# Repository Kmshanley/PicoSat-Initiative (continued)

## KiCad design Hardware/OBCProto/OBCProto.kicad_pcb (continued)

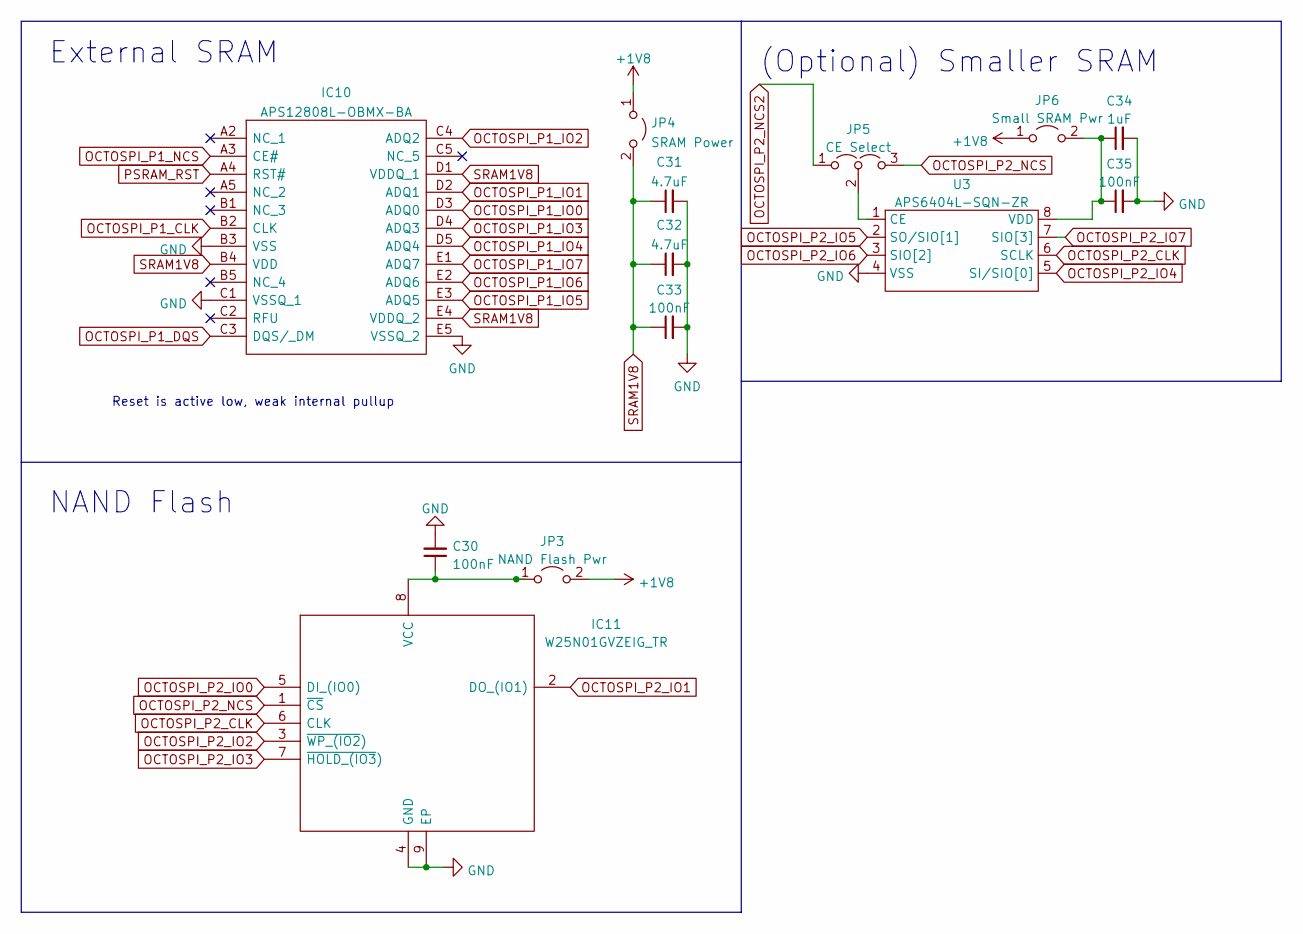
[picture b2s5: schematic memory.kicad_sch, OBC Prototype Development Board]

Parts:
C30, C33, C35: 100nF; C_0402_1005Metric
C31, C32: 4.7uF; C_0402_1005Metric
C34: 1uF; C_0402_1005Metric
IC10: APS12808L-OBMX-BA; BGA24C100P5X5_600X800X120; Mouser Part Number 878-APS12808L-OBMXBA
IC11: W25N01GVZEIG_TR; SON127P800X600X80-9N-D; Mouser Part Number 454-W25N01GVZEIGTR
JP3: NAND Flash Pwr; PinHeader_1x02_P2.54mm_Vertical
JP4: SRAM Power; PinHeader_1x02_P2.54mm_Vertical
JP5: CE Select; PinHeader_1x03_P2.54mm_Vertical
JP6: Small SRAM Pwr; PinHeader_1x02_P2.54mm_Vertical
U3: APS6404L-SQN-ZR

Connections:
+1V8: JP3.2 (B), JP4.1 (A), JP6.1 (A); also elsewhere on the board
GND: C30.2, C31.2, C32.2, C33.2, C34.2, C35.2, IC10.B3 (VSS), IC10.C1 (VSSQ_1), IC10.E5 (VSSQ_2), IC11.4 (GND), IC11.9 (EP), U3.4 (VSS); also elsewhere on the board
unnamed: C30.1, IC11.8 (VCC), JP3.1 (A)
unnamed: C34.1, C35.1, JP6.2 (B), U3.8 (VDD)
unnamed: JP5.2 (C), U3.1 (CE)
OCTOSPI_P1_CLK: IC10.B2 (CLK); also elsewhere on the board
OCTOSPI_P1_DQS: IC10.C3 (DQS/_DM); also elsewhere on the board
OCTOSPI_P1_IO0: IC10.D3 (ADQ0); also elsewhere on the board
OCTOSPI_P1_IO1: IC10.D2 (ADQ1); also elsewhere on the board
OCTOSPI_P1_IO2: IC10.C4 (ADQ2); also elsewhere on the board
OCTOSPI_P1_IO3: IC10.D4 (ADQ3); also elsewhere on the board
OCTOSPI_P1_IO4: IC10.D5 (ADQ4); also elsewhere on the board
OCTOSPI_P1_IO5: IC10.E3 (ADQ5); also elsewhere on the board
OCTOSPI_P1_IO6: IC10.E2 (ADQ6); also elsewhere on the board
OCTOSPI_P1_IO7: IC10.E1 (ADQ7); also elsewhere on the board
OCTOSPI_P1_NCS: IC10.A3 (CE#); also elsewhere on the board
OCTOSPI_P2_CLK: IC11.6 (CLK), U3.6 (SCLK); also elsewhere on the board
OCTOSPI_P2_IO0: IC11.5 (DI_(IO0)); also elsewhere on the board
OCTOSPI_P2_IO1: IC11.2 (DO_(IO1)); also elsewhere on the board
OCTOSPI_P2_IO2: IC11.3 (~WP_(IO2)); also elsewhere on the board
OCTOSPI_P2_IO3: IC11.7 (~HOLD_(IO3)); also elsewhere on the board
OCTOSPI_P2_IO4: U3.5 (SI/SIO[0]); also elsewhere on the board
OCTOSPI_P2_IO5: U3.2 (SO/SIO[1]); also elsewhere on the board
OCTOSPI_P2_IO6: U3.3 (SIO[2]); also elsewhere on the board
OCTOSPI_P2_NCS: IC11.1 (~CS), JP5.3 (B); also elsewhere on the board
OCTOSPI_P2_NCS2: JP5.1 (A); also elsewhere on the board
PSRAM_RST: IC10.A4 (RST#); also elsewhere on the board
SRAM1V8: C31.1, C32.1, C33.1, IC10.B4 (VDD), IC10.D1 (VDDQ_1), IC10.E4 (VDDQ_2), JP4.2 (B)

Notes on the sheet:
External SRAM
Reset is active low, weak internal pullup
(Optional) Smaller SRAM
NAND Flash

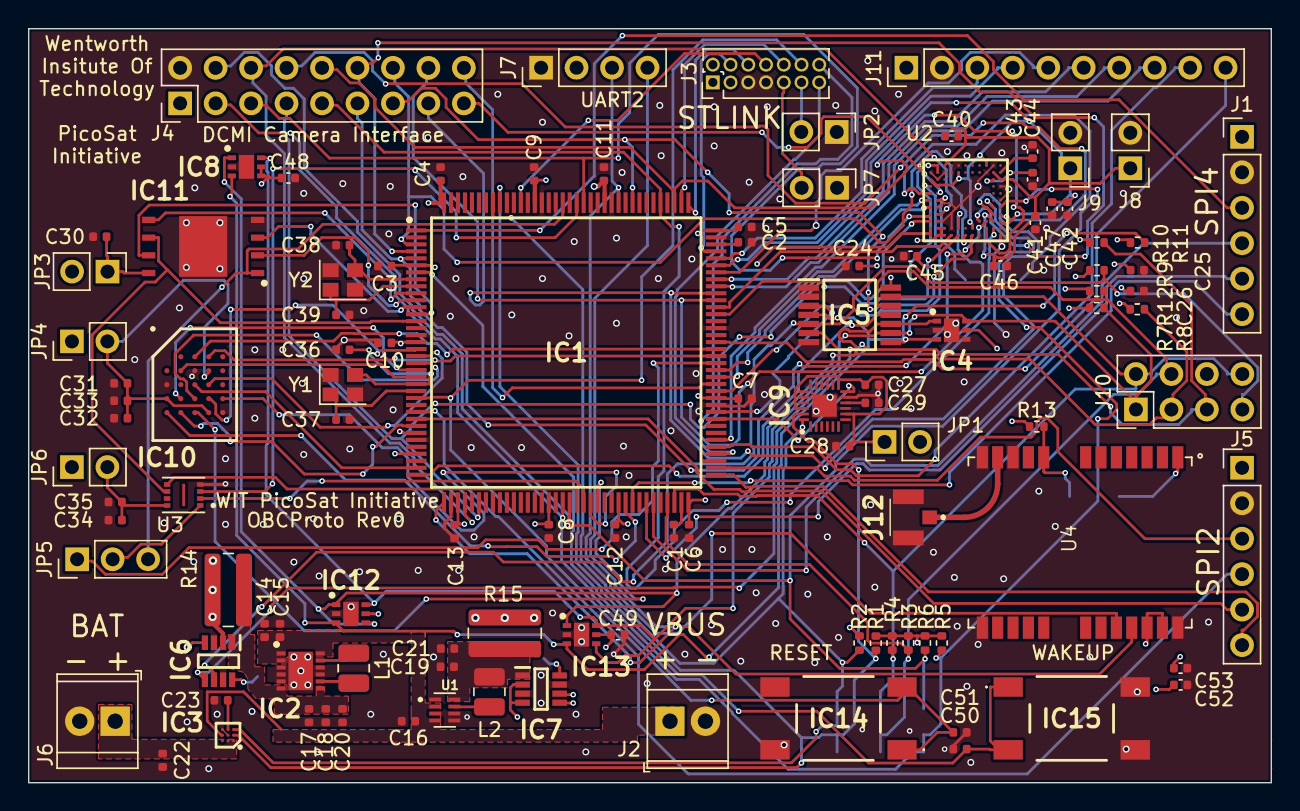
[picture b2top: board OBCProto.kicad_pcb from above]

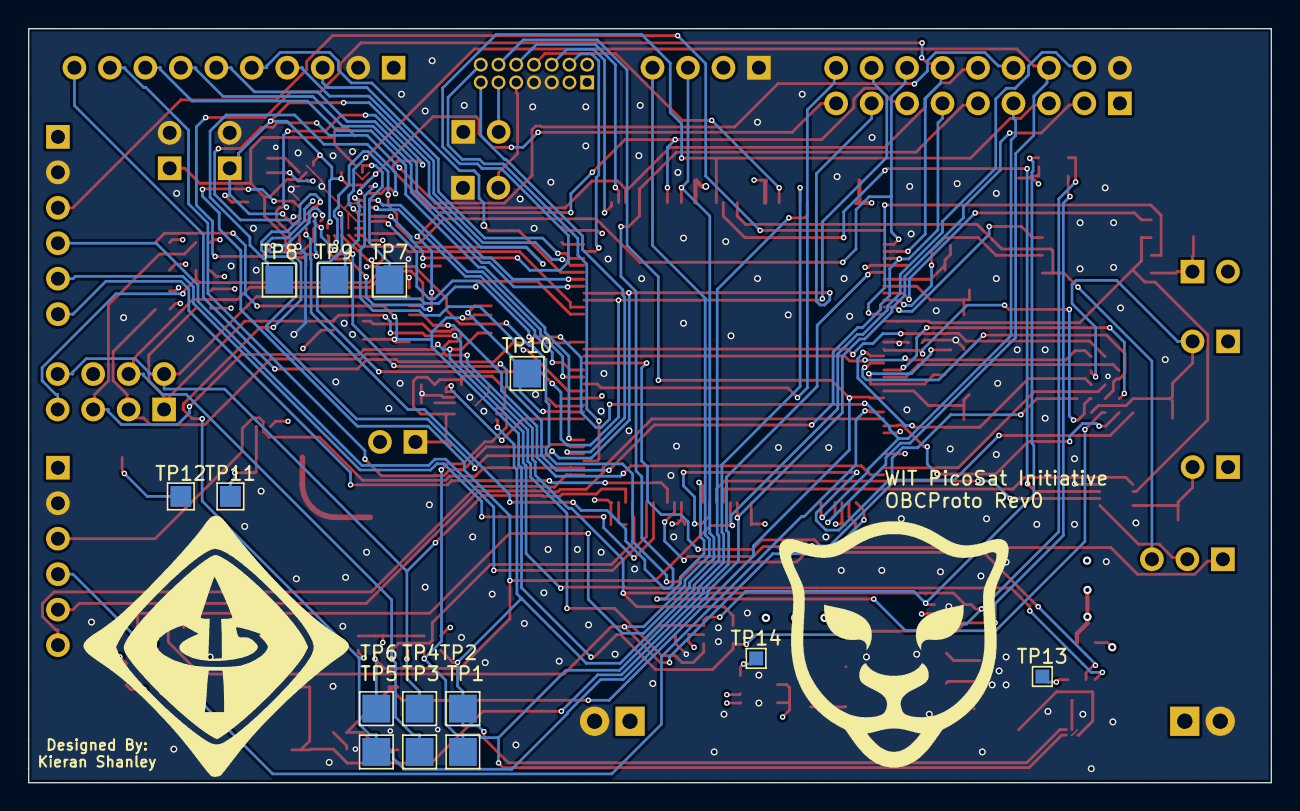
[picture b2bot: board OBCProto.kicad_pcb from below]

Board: 4 copper layers, 89.0 x 54.0 mm, 124 parts (14 on the bottom side), 118 nets.

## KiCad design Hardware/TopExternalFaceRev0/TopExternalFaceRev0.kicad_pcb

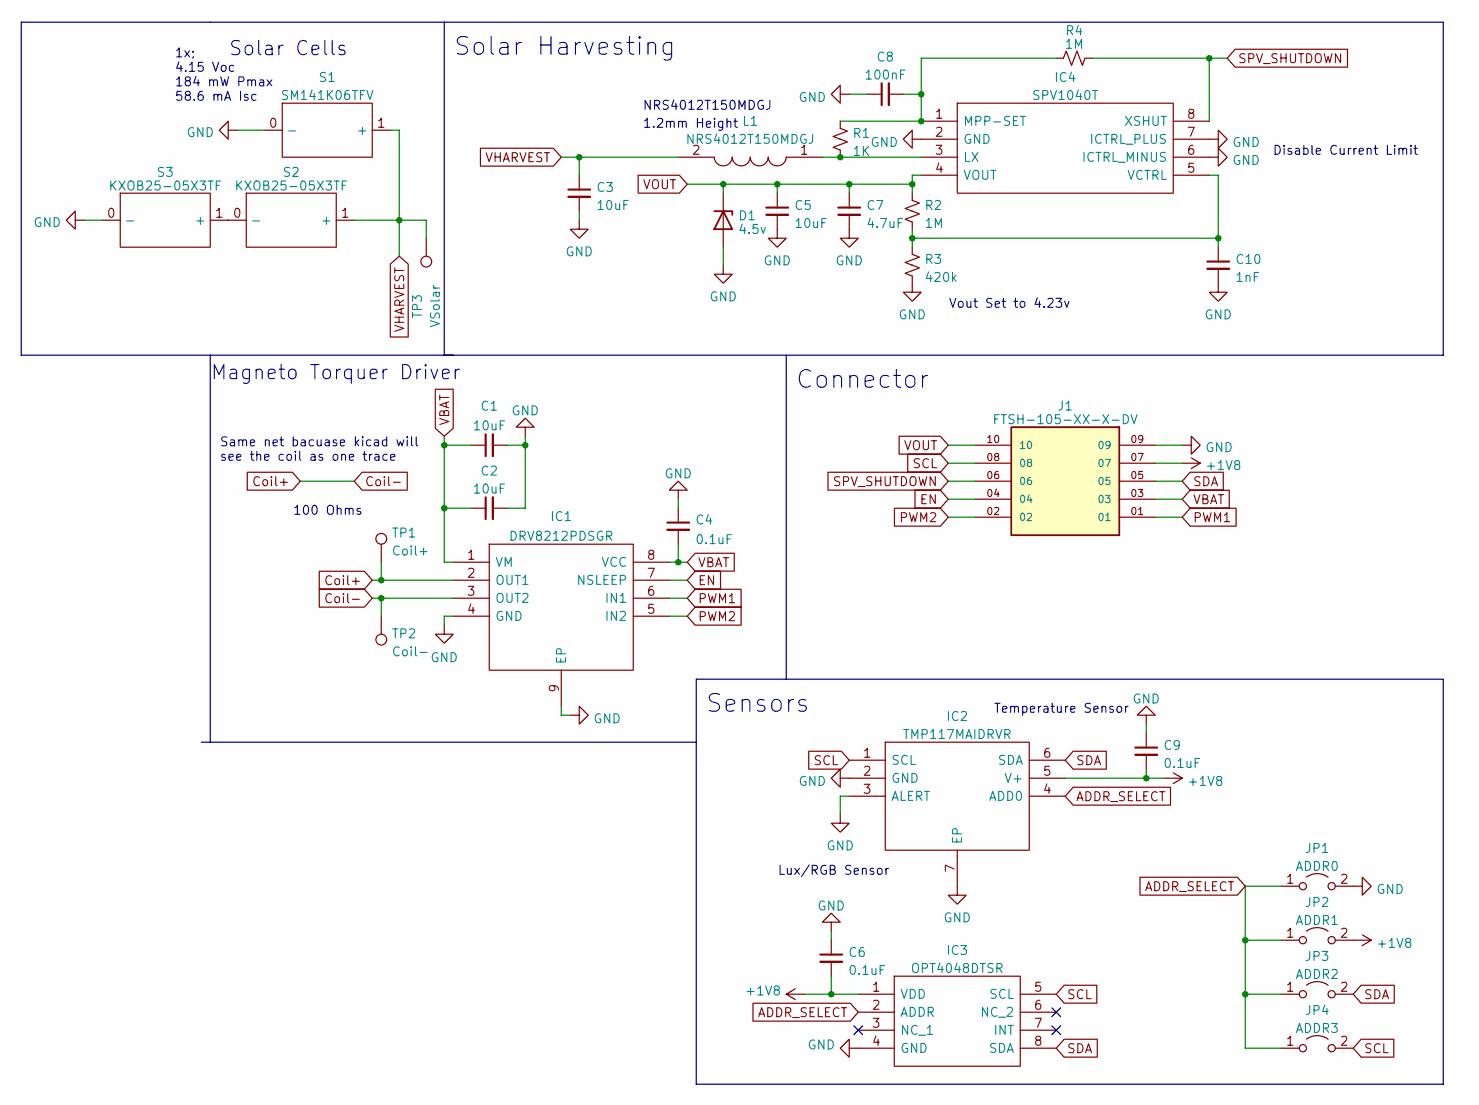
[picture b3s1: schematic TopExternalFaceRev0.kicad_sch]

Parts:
C1, C2, C3, C5: 10uF; C_0402_1005Metric
C4, C6, C9: 0.1uF; C_0402_1005Metric
C7: 4.7uF; C_0402_1005Metric
C8: 100nF; C_0402_1005Metric
C10: 1nF; C_0402_1005Metric
D1: 4.5v; D_SOD-123
IC1: DRV8212PDSGR; SON50P200X200X80-9N; Mouser Part Number 595-DRV8212PDSGR
IC2: TMP117MAIDRVR; SON65P200X200X80-7N; Mouser Part Number 595-TMP117MAIDRVR
IC3: OPT4048DTSR; SOTFL50P190X60-8N; Mouser Part Number 595-OPT4048DTSR
IC4: SPV1040T; SOP65P640X120-8N; Mouser Part Number 511-SPV1040T
J1: FTSH-105-XX-X-DV; SAMTEC_FTSH-105-XX-X-DV; PARTREV H
JP1: ADDR0; SolderJumper-2_P1.3mm_Open_Pad1.0x1.5mm
JP2: ADDR1; SolderJumper-2_P1.3mm_Open_Pad1.0x1.5mm
JP3: ADDR2; SolderJumper-2_P1.3mm_Open_Pad1.0x1.5mm
JP4: ADDR3; SolderJumper-2_P1.3mm_Open_Pad1.0x1.5mm
L1: NRS4012T150MDGJ; Mouser Part Number 963-NRS4012T150MDGJ
R1: 1K; R_0402_1005Metric
R2, R4: 1M; R_0402_1005Metric
R3: 420k; R_0402_1005Metric
S1: SM141K06TFV
S2, S3: KXOB25-05X3TF
TP1: Coil+; TestPoint_Pad_D2.0mm
TP2: Coil-; TestPoint_Pad_D2.0mm
TP3: VSolar; TestPoint_Pad_1.0x1.0mm

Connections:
+1V8: C6.2, C9.2, IC2.5 (V+), IC3.1 (VDD), J1.07, JP2.2 (B)
ADDR_SELECT: IC2.4 (ADD0), IC3.2 (ADDR), JP1.1 (A), JP2.1 (A), JP3.1 (A), JP4.1 (A)
Coil+: IC1.2 (OUT1), IC1.3 (OUT2), TP1.1, TP2.1
EN: IC1.7 (NSLEEP), J1.04
GND: C1.2, C2.2, C3.2, C4.1, C5.2, C6.1, C7.2, C8.1, C9.1, C10.2, D1.2 (A), IC1.4 (GND), IC1.9 (EP), IC2.2 (GND), IC2.3 (ALERT), IC2.7 (EP), IC3.4 (GND), IC4.2 (GND), IC4.6 (ICTRL_MINUS), IC4.7 (ICTRL_PLUS), J1.09, JP1.2 (B), R3.2, S1.0 (-), S3.0 (-)
unnamed: IC4.3 (LX), L1.1, R1.2
unnamed: C8.2, IC4.1 (MPP-SET), R1.1, R4.1
unnamed: C10.1, IC4.5 (VCTRL), R2.2, R3.1
unnamed: S2.0 (-), S3.1 (+)
PWM1: IC1.6 (IN1), J1.01
PWM2: IC1.5 (IN2), J1.02
SCL: IC2.1 (SCL), IC3.5 (SCL), J1.08, JP4.2 (B)
SDA: IC2.6 (SDA), IC3.8 (SDA), J1.05, JP3.2 (B)
SPV_SHUTDOWN: IC4.8 (XSHUT), J1.06, R4.2
VBAT: C1.1, C2.1, C4.2, IC1.1 (VM), IC1.8 (VCC), J1.03
VHARVEST: C3.1, L1.2, S1.1 (+), S2.1 (+), TP3.1
VOUT: C5.1, C7.1, D1.1 (K), IC4.4 (VOUT), J1.10, R2.1

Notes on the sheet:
Lux/RGB Sensor
Sensors
100 Ohms
Vout Set to 4.23v
Solar Cells
Disable Current Limit
1.2mm Height
Solar Harvesting
NRS4012T150MDGJ
Same net bacuase kicad will see the coil as one trace
Magneto Torquer Driver
Connector
1x; 4.15 Voc 184 mW Pmax 58.6 mA Isc
Temperature Sensor

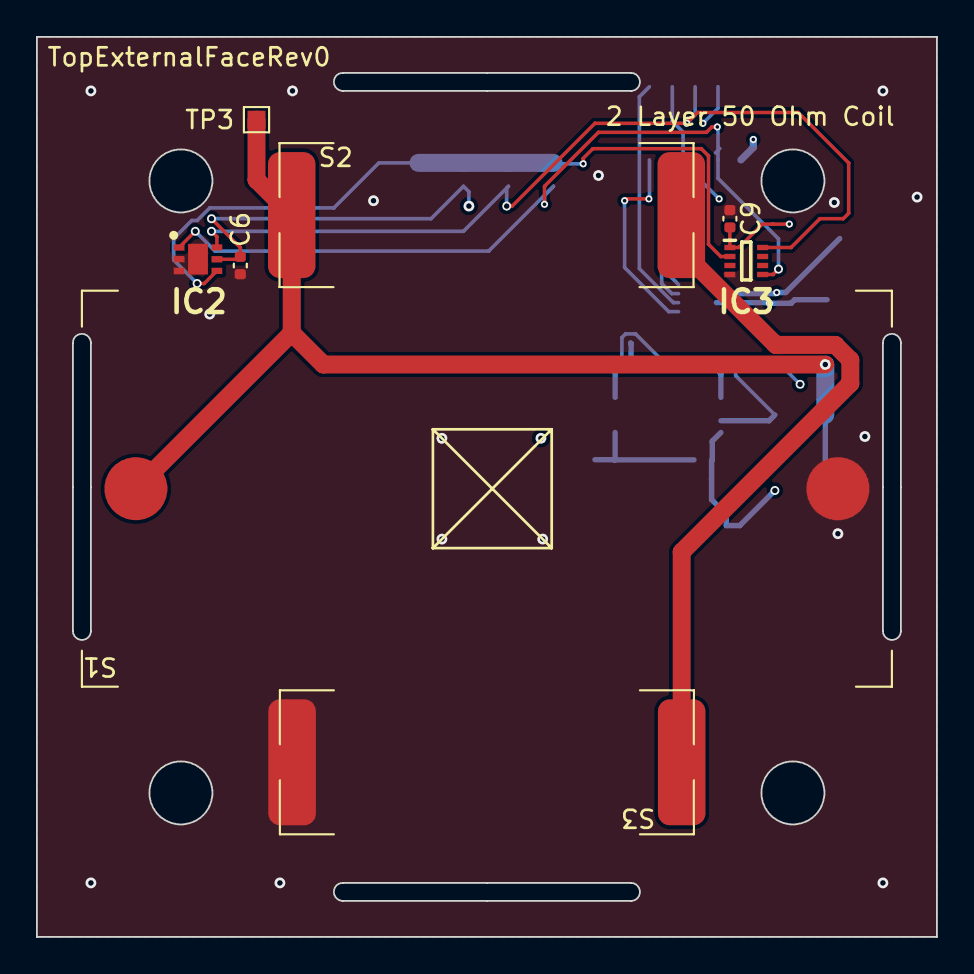
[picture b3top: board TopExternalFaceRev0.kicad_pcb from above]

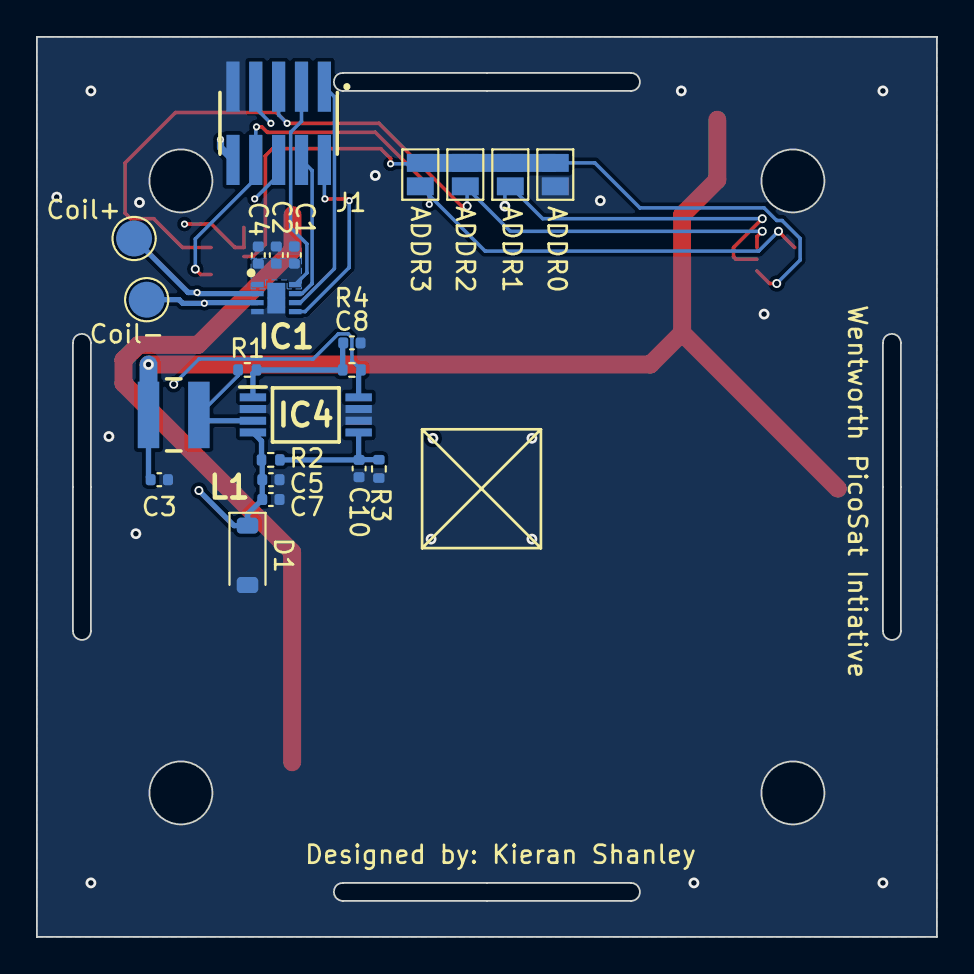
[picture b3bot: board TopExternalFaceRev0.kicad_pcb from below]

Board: 4 copper layers, 50.0 x 50.0 mm, 31 parts (23 on the bottom side), 17 nets.

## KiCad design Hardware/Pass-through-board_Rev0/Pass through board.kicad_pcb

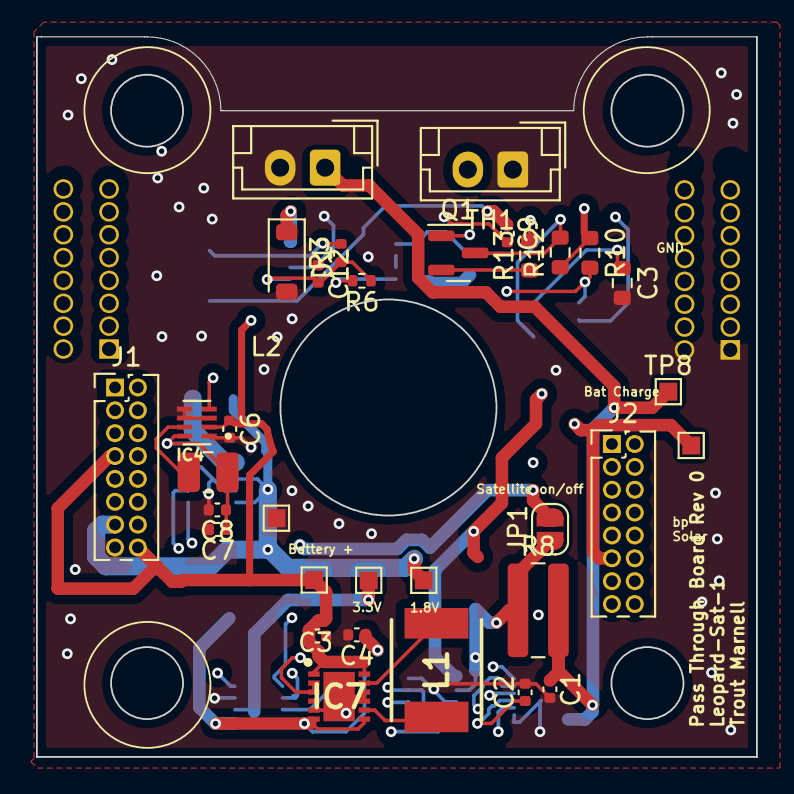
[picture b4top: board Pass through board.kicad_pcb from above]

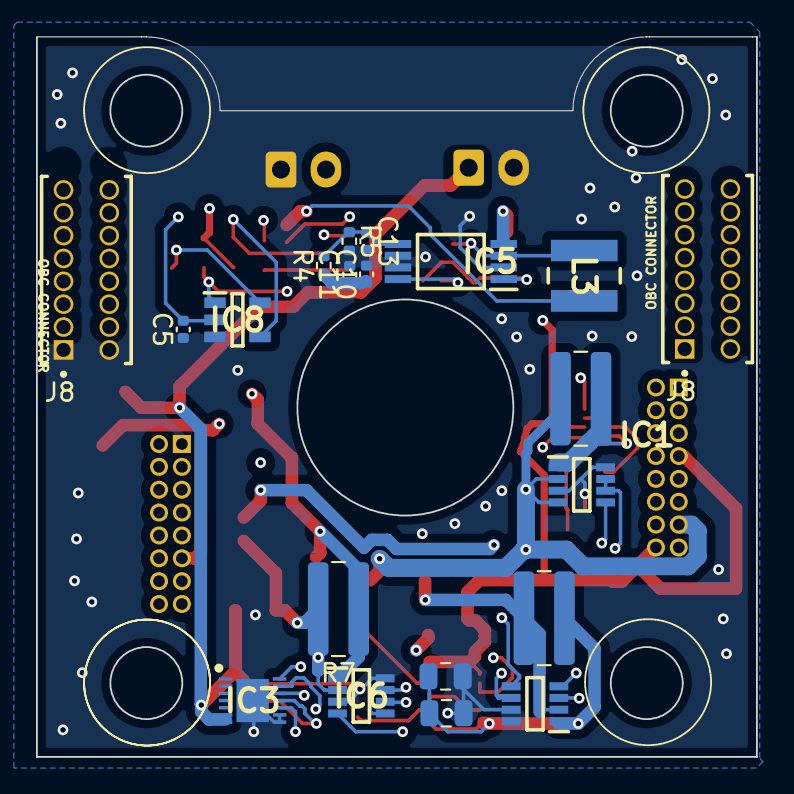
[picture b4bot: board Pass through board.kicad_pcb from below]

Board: 4 copper layers, 40.0 x 40.0 mm, 53 parts (20 on the bottom side), 26 nets.

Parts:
C1: .1uF; C_0402_1005Metric
C2: .47uF; C_0402_1005Metric
C3: 10uF; R_0603_1608Metric
C3#2, C7, C9, C10: 10uF; C_0402_1005Metric
C4: 22uF; C_0402_1005Metric
C5, C8: 1uF; C_0402_1005Metric
C6, C11: 4.7uF; C_0402_1005Metric
C12: 100nF; C_0402_1005Metric
C13: 1nF; C_0402_1005Metric
D1: 4.5v; D_SOD-123
IC1, IC2, IC6: INA236AIDDFR; SOP65P280X110-8N
IC3: MAX17260SETD+T; SON40P300X300X80-15N
IC4: TPS62840DLCR; SON50P200X150X100-8N
IC5: SPV1040T; SOP65P640X120-8N
IC7: RP602K330G-TR; SON50P270X300X60-13N
IC8: TLV840MADL30DBVRQ1; SOT95P280X145-5N
J1, J2: FLE-108-01-XX-DV; PinHeader_2x08_P1.27mm_Vertical
J3: Conn_01x02_Socket; JST_EH_B2B-EH-A_1x02_P2.50mm_Vertical
J8, J8#2: SLM-108-01-L-D; SAMTEC_SLM-108-01-L-D
JP1: SolderJumper_2_Open; SolderJumper-2_P1.3mm_Open_RoundedPad1.0x1.5mm
L1: 1.0uH; INDPM5650X530N
L2: 2.2uH; L_1008_2520Metric
L3: NRS4012T150MDGJ
Q1: 2N7002; SOT-23
R1, R2, R7: 20m; R_1020_2550Metric
R3: 1K; R_0402_1005Metric
R4, R6: 1M; R_0402_1005Metric
R5: 420k; R_0402_1005Metric
R8: 10m; R_1020_2550Metric
R10, R12: 1M; R_0603_1608Metric
R13: 5k; R_0603_1608Metric
TH1: Thermistor_NTC 10k; JST_EH_B2B-EH-A_1x02_P2.50mm_Vertical
TP1, TP2, TP3, TP4, TP6, TP8: TestPoint_Alt; TestPoint_Pad_1.0x1.0mm
ff: C_0805_2012Metric
gg: C_0805_2012Metric

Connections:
1.8V: IC1.4 (VS), IC2.2 (IN-), IC2.4 (VS), IC6.4 (VS), J1.13, J2.5, Q1.1 (G), R2.2, R13.2, TP3.1
1V8 MEASURE: C7.1, C8.1, IC2.1 (IN+), IC4.8 (VOS), L2.2, R2.1
3.3V: C5.2, IC1.2 (IN-), IC8.2 (VDD), R1.2, TP2.1
3V3 MEASURE: C4.1, IC1.1 (IN+), IC7.6 (VFB), IC7.7 (VOUT), R1.1, ff.1, gg.1
Battery +: C3#2.2, C6.1, IC4.2 (VIN), IC7.1 (AVIN), IC7.12 (PVIN), J1.7, J1.16, R10.1, R12.1, TP1.1
Battery Charge: C1.1, IC3.6 (BATT), IC3.7 (CSN), J3.1, R8.2, TP8.1
CONV_SHUTDOWN: IC4.4 (EN), IC7.2 (CE), IC7.3 (MODE), IC8.1 (~RESET_/_RESET), R10.2
CT: C3.1, IC8.5 (CT)
GND: C1.2, C2.2, C3.2, C3#2.1, C4.2, C5.1, C6.2, C7.2, C8.2, C9.2, C10.2, C11.2, C12.1, C13.2, D1.2 (A), IC1.3 (GND), IC1.7 (A0), IC1.8 (ALERT), IC2.3 (GND), IC2.8 (ALERT), IC3.8 (GND), IC3.9 (CSPL), IC3.15 (EP), IC4.1 (GND), IC4.3 (MODE), IC4.5 (VSET), IC4.6 (STOP), IC5.2 (GND), IC5.6 (ICTRL_MINUS), IC5.7 (ICTRL_PLUS), IC6.3 (GND), IC6.8 (ALERT), IC7.5 (AGND), IC7.9 (PGND_1), IC7.10 (PGND_2), IC7.13 (GROUND), IC8.3 (GND), J1.15, J2.1, J3.2, R5.2, TH1.1, TP4.1, ff.2, gg.2
MPPT ENABLE: IC5.8 (XSHUT), R6.2
unnamed: C2.1, IC3.11 (REG)
unnamed: IC3.1 (TH), TH1.2
unnamed: IC4.7 (SW), L2.1
unnamed: IC5.3 (LX), L3.1, R3.2
unnamed: C12.2, IC5.1 (MPP-SET), R3.1, R6.1
unnamed: C13.1, IC5.5 (VCTRL), R4.2, R5.1
unnamed: IC7.8 (BOLX), L1.2
unnamed: IC7.11 (BULX), L1.1
unnamed: IC8.4 (~MR), Q1.3 (D), R12.2
SAT_REST: Q1.2 (S), R13.1
SCL(1): IC1.5 (SCL), IC2.5 (SCL), IC3.14 (SCL), IC6.5 (SCL), IC6.7 (A0), J1.1
SDA(1): IC1.6 (SDA), IC2.6 (SDA), IC2.7 (A0), IC3.13 (SDA), IC6.6 (SDA), J1.3
VBAT+: J1.14, J2.3, JP1.2 (B)
VMPPT: C10.1, C11.1, D1.1 (K), IC5.4 (VOUT), IC6.1 (IN+), J2.9, R4.1, R7.1
VMPPTCHARGE: IC3.10 (CSPH), IC6.2 (IN-), JP1.1 (A), R7.2, R8.1
Vsolar: C9.1, J2.11, L3.2, TP6.1

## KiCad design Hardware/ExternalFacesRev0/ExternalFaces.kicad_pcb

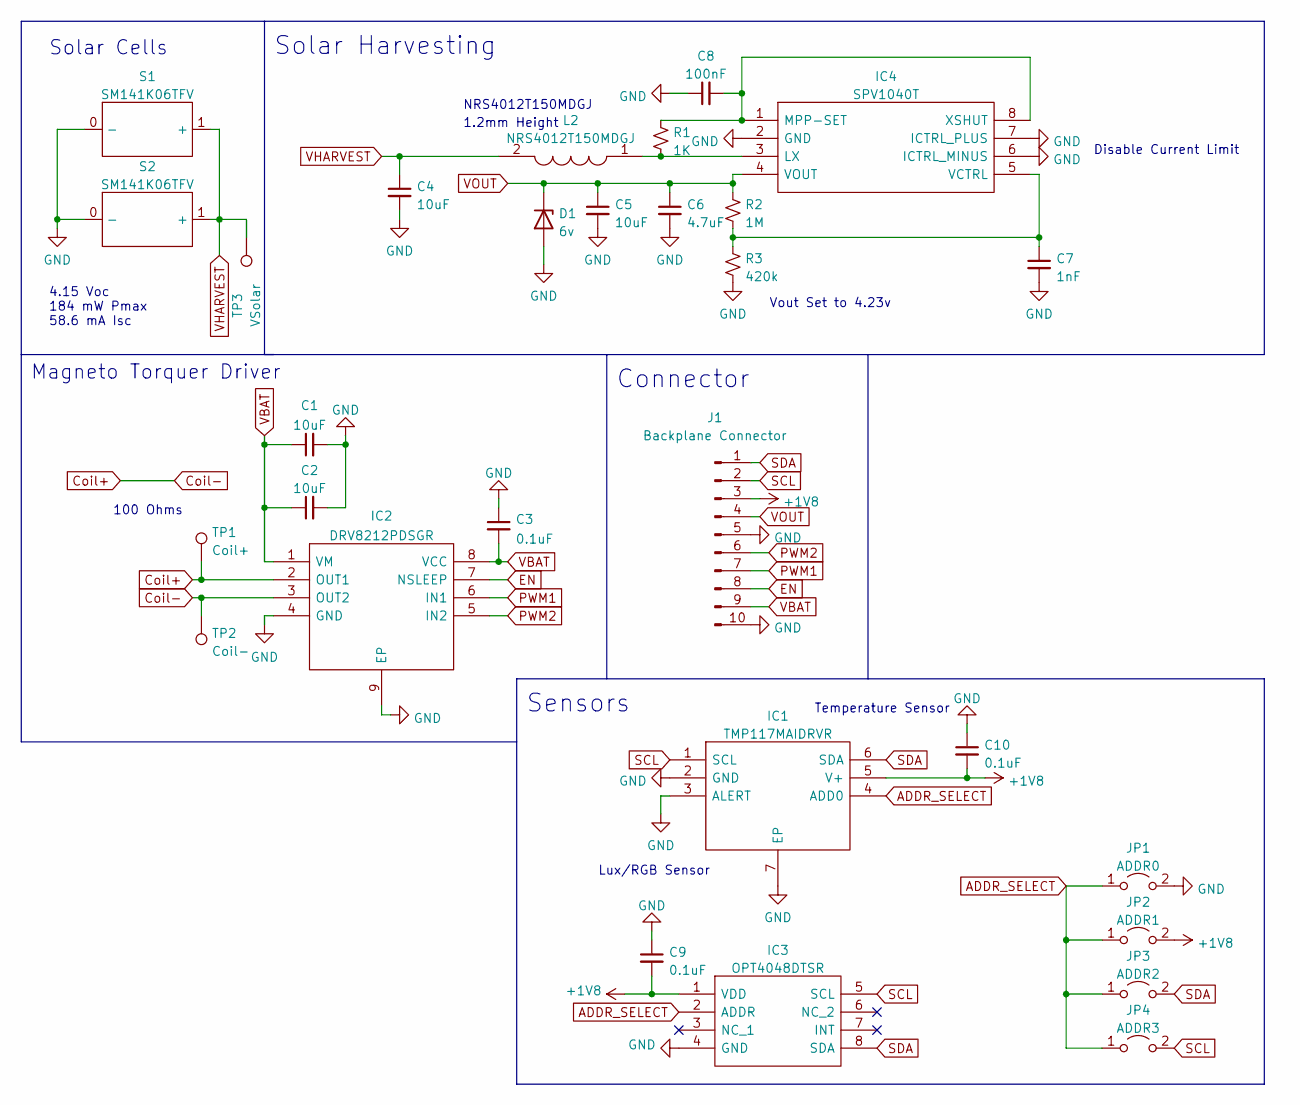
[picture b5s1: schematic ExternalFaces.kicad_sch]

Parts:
C1, C2, C4, C5: 10uF; C_0402_1005Metric
C3, C9, C10: 0.1uF; C_0402_1005Metric
C6: 4.7uF; C_0402_1005Metric
C7: 1nF; C_0402_1005Metric
C8: 100nF; C_0402_1005Metric
D1: 6v; D_SOD-123
IC1: TMP117MAIDRVR; SON65P200X200X80-7N; Mouser Part Number 595-TMP117MAIDRVR
IC2: DRV8212PDSGR; SON50P200X200X80-9N; Mouser Part Number 595-DRV8212PDSGR
IC3: OPT4048DTSR; SOTFL50P190X60-8N; Mouser Part Number 595-OPT4048DTSR
IC4: SPV1040T; SOP65P640X120-8N; Mouser Part Number 511-SPV1040T
J1: Backplane Connector; PinHeader_1x10_P1.00mm_Vertical
JP1: ADDR0; SolderJumper-2_P1.3mm_Open_Pad1.0x1.5mm
JP2: ADDR1; SolderJumper-2_P1.3mm_Open_Pad1.0x1.5mm
JP3: ADDR2; SolderJumper-2_P1.3mm_Open_Pad1.0x1.5mm
JP4: ADDR3; SolderJumper-2_P1.3mm_Open_Pad1.0x1.5mm
L2: NRS4012T150MDGJ; Mouser Part Number 963-NRS4012T150MDGJ
R1: 1K; R_0402_1005Metric
R2: 1M; R_0402_1005Metric
R3: 420k; R_0402_1005Metric
S1, S2: SM141K06TFV
TP1: Coil+; TestPoint_Pad_D2.0mm
TP2: Coil-; TestPoint_Pad_D2.0mm
TP3: VSolar; TestPoint_Pad_1.0x1.0mm

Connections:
+1V8: C9.2, C10.2, IC1.5 (V+), IC3.1 (VDD), J1.3, JP2.2 (B)
ADDR_SELECT: IC1.4 (ADD0), IC3.2 (ADDR), JP1.1 (A), JP2.1 (A), JP3.1 (A), JP4.1 (A)
Coil+: IC2.2 (OUT1), IC2.3 (OUT2), TP1.1, TP2.1
EN: IC2.7 (NSLEEP), J1.8
GND: C1.2, C2.2, C3.1, C4.2, C5.2, C6.2, C7.2, C8.1, C9.1, C10.1, D1.2 (A), IC1.2 (GND), IC1.3 (ALERT), IC1.7 (EP), IC2.4 (GND), IC2.9 (EP), IC3.4 (GND), IC4.2 (GND), IC4.6 (ICTRL_MINUS), IC4.7 (ICTRL_PLUS), J1.5, J1.10, JP1.2 (B), R3.2, S1.0 (-), S2.0 (-)
unnamed: C7.1, IC4.5 (VCTRL), R2.2, R3.1
unnamed: C8.2, IC4.1 (MPP-SET), IC4.8 (XSHUT), R1.1
unnamed: IC4.3 (LX), L2.1, R1.2
PWM1: IC2.6 (IN1), J1.7
PWM2: IC2.5 (IN2), J1.6
SCL: IC1.1 (SCL), IC3.5 (SCL), J1.2, JP4.2 (B)
SDA: IC1.6 (SDA), IC3.8 (SDA), J1.1, JP3.2 (B)
VBAT: C1.1, C2.1, C3.2, IC2.1 (VM), IC2.8 (VCC), J1.9
VHARVEST: C4.1, L2.2, S1.1 (+), S2.1 (+), TP3.1
VOUT: C5.1, C6.1, D1.1 (K), IC4.4 (VOUT), J1.4, R2.1

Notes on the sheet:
Lux/RGB Sensor
4.15 Voc 184 mW Pmax 58.6 mA Isc
1.2mm Height
Solar Harvesting
Magneto Torquer Driver
Vout Set to 4.23v
Solar Cells
Sensors
Temperature Sensor
Disable Current Limit
Connector
100 Ohms
NRS4012T150MDGJ

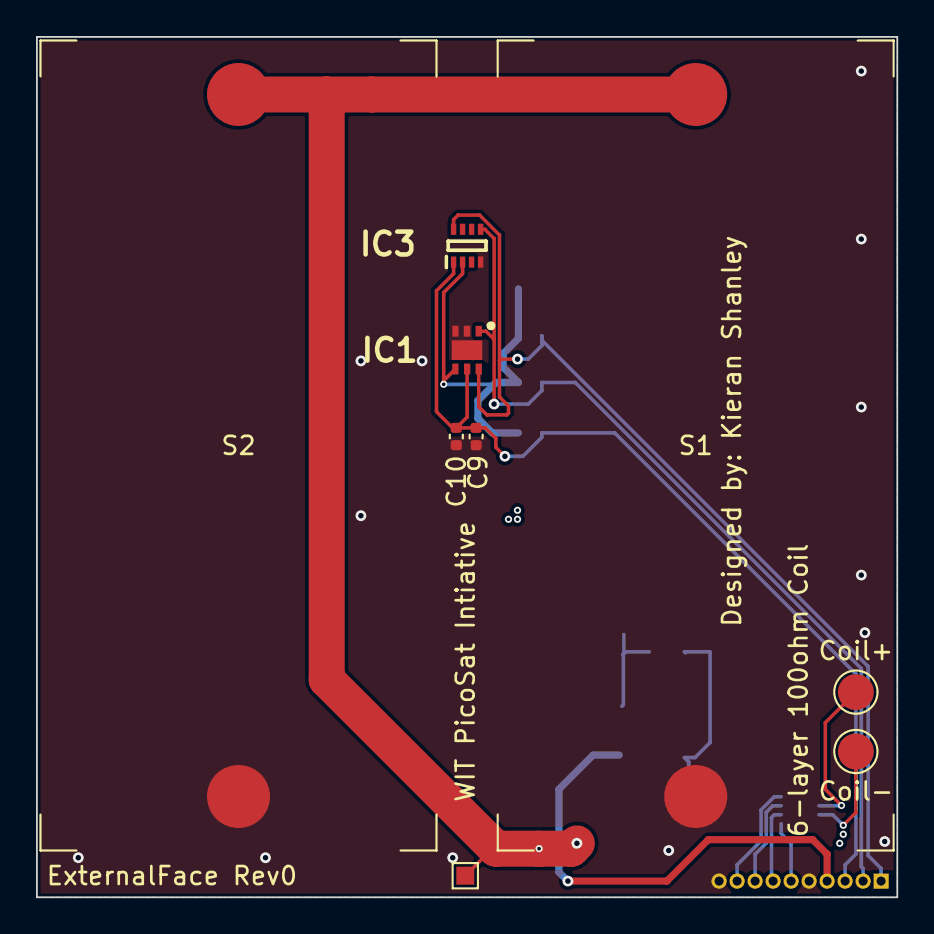
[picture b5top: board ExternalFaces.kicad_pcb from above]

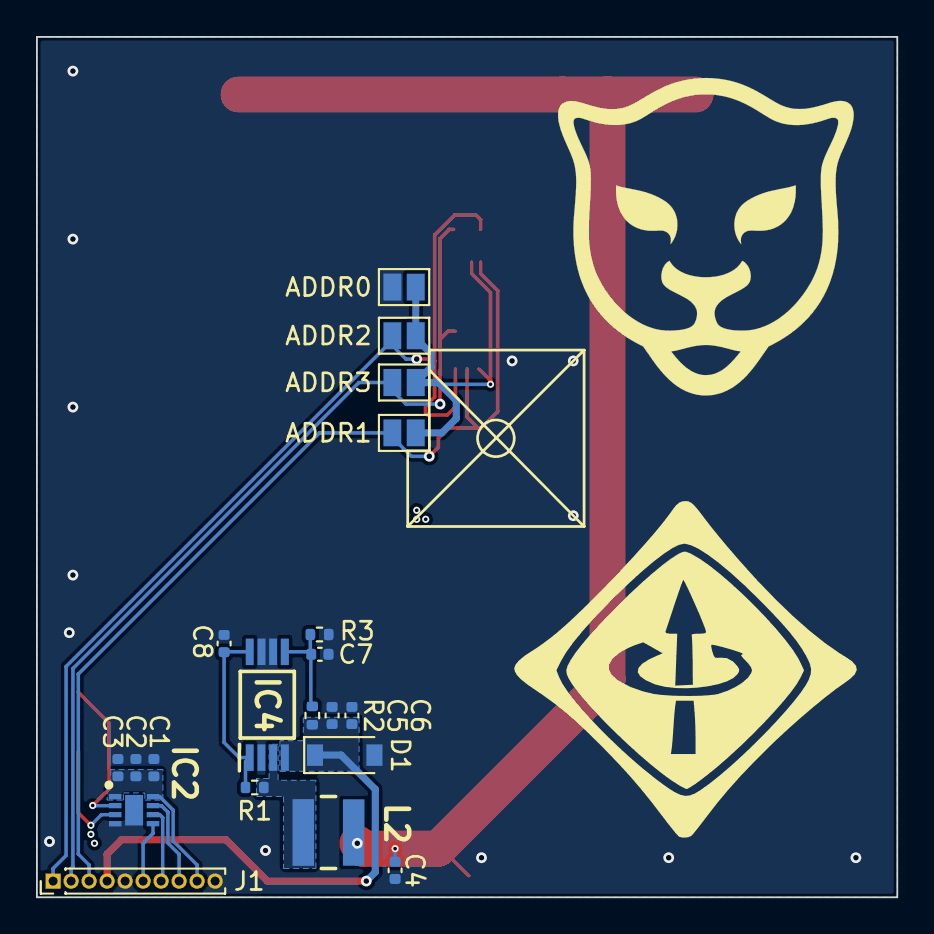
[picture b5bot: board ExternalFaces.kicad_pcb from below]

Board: 8 copper layers, 47.8 x 47.8 mm, 29 parts (20 on the bottom side), 15 nets.

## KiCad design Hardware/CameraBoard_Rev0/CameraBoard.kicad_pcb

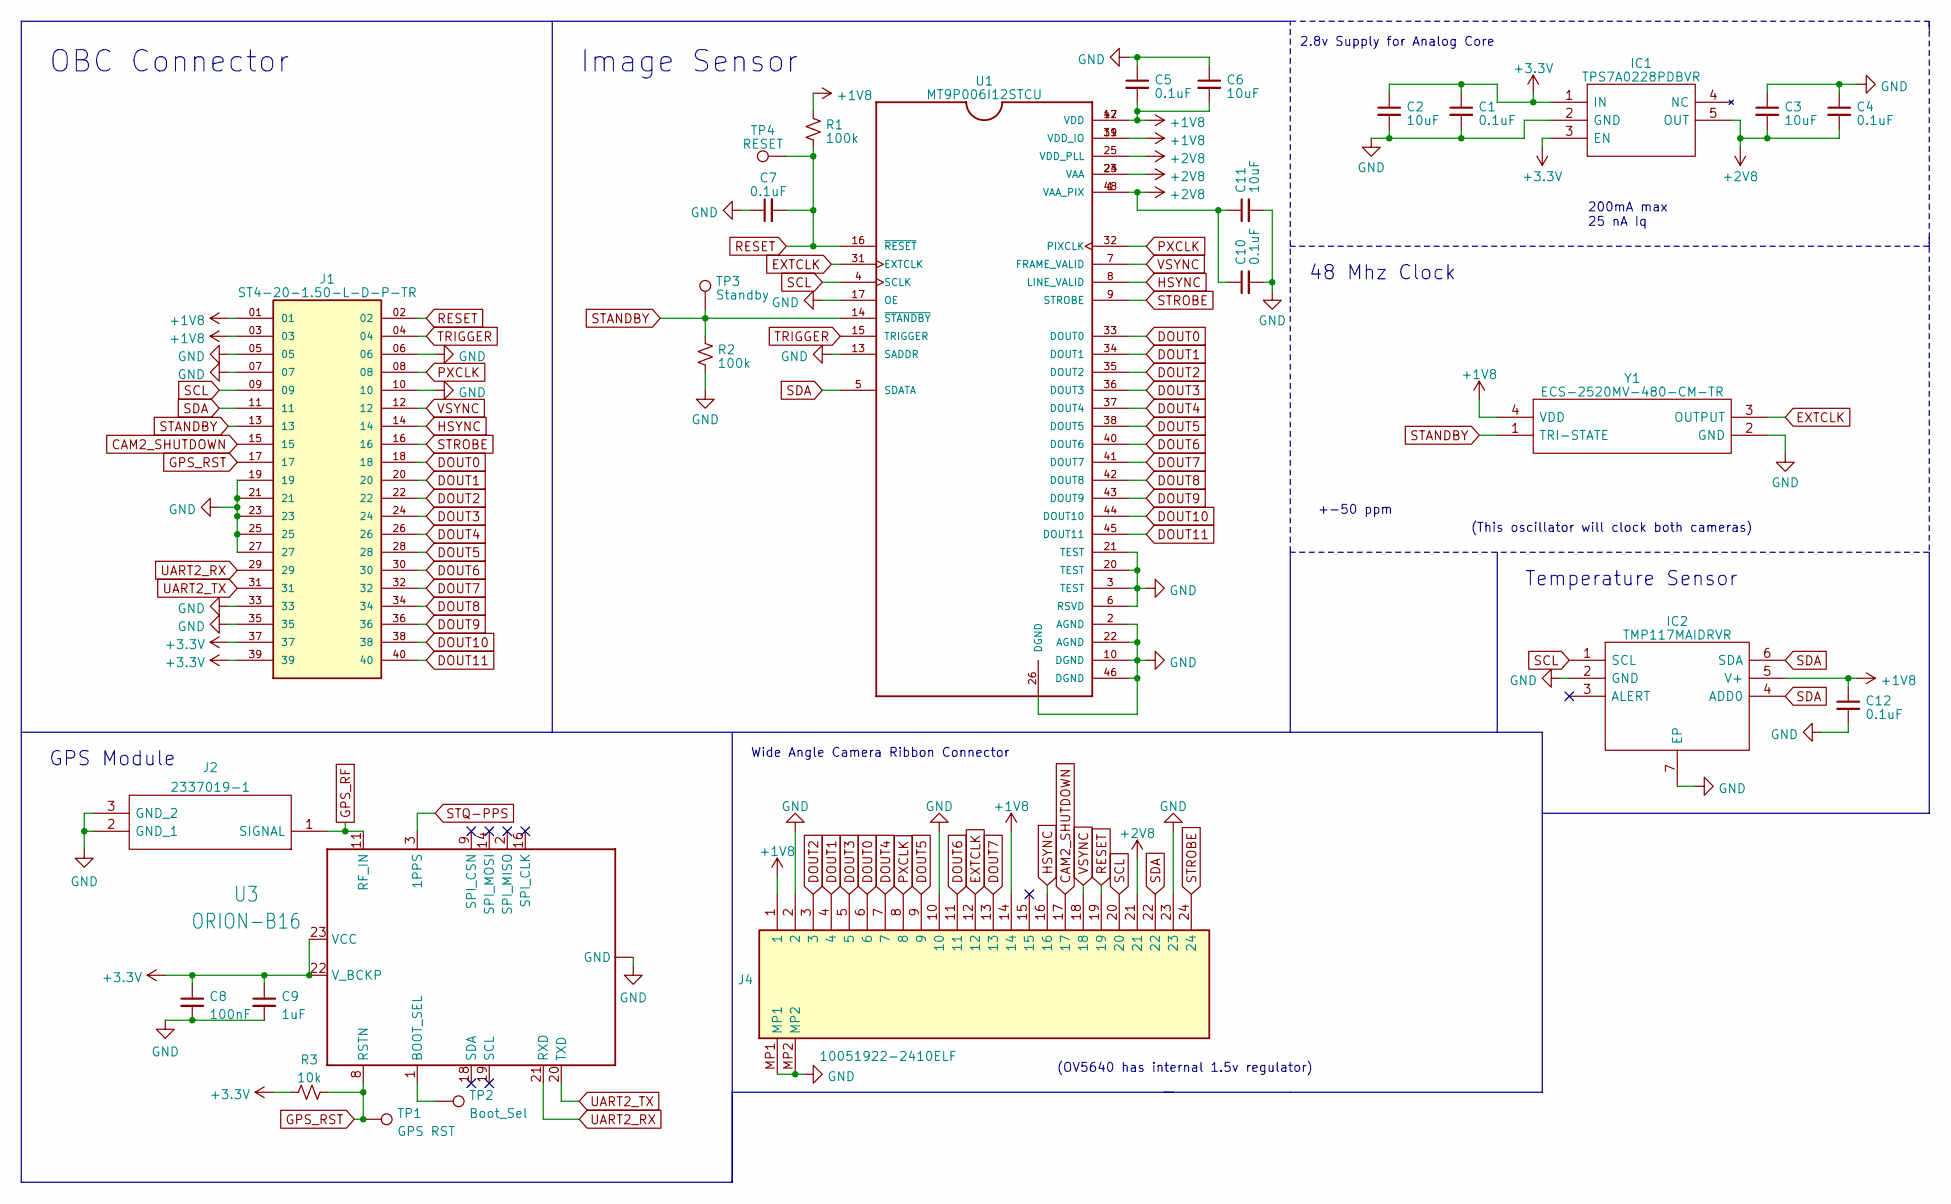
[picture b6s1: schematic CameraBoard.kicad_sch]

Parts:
C1, C4, C5, C7, C10, C12: 0.1uF; C_0402_1005Metric
C2, C3, C6, C11: 10uF; C_0402_1005Metric
C8: 100nF; C_0402_1005Metric
C9: 1uF; C_0402_1005Metric
IC1: TPS7A0228PDBVR; SOT95P280X145-5N; Mouser Part Number 595-TPS7A0228PDBVR
IC2: TMP117MAIDRVR; SON65P200X200X80-7N; Mouser Part Number 595-TMP117MAIDRVR
J1: ST4-20-1.50-L-D-P-TR; SAMTEC_ST4-20-1.50-L-D-P-TR; PARTREV J
J2: 2337019-1; 23370191; Mouser Part Number 571-2337019-1
J4: 10051922-2410ELF; 100519222410ELF; Mouser Part Number 649-10051922-2410ELF
R1, R2: 100k; R_0402_1005Metric
R3: 10k; R_0402_1005Metric
TP1: GPS RST; TestPoint_Pad_1.0x1.0mm
TP2: Boot_Sel; TestPoint_Pad_1.0x1.0mm
TP3: Standby; TestPoint_Pad_1.0x1.0mm
TP4: RESET; TestPoint_Pad_1.0x1.0mm
U1: MT9P006I12STCU; LCC70P1000X1000X125-48N
U3: ORION-B16; U-SkyTraq-ORION-B16
Y1: ECS-2520MV-480-CM-TR; ECS2520MV480CMTR; Mouser Part Number 520-2520MV-480-CM-TR

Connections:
+1V8: C5.2, C6.2, C12.1, IC2.5 (V+), J1.01, J1.03, J4.1, J4.14, R1.1, U1.11 (VDD_IO), U1.12 (VDD), U1.39 (VDD_IO), U1.47 (VDD), Y1.4 (VDD)
+2V8: C3.2, C4.2, C10.1, C11.1, IC1.5 (OUT), J4.21, U1.1 (VAA_PIX), U1.23 (VAA), U1.24 (VAA), U1.25 (VDD_PLL), U1.48 (VAA_PIX)
+3.3V: C1.1, C2.1, C8.1, C9.1, IC1.1 (IN), IC1.3 (EN), J1.37, J1.39, R3.1, U3.22 (V_BCKP), U3.23 (VCC)
CAM2_SHUTDOWN: J1.15, J4.17
DOUT0: J1.18, J4.6, U1.33 (DOUT0)
DOUT1: J1.20, J4.4, U1.34 (DOUT1)
DOUT2: J1.22, J4.3, U1.35 (DOUT2)
DOUT3: J1.24, J4.5, U1.36 (DOUT3)
DOUT4: J1.26, J4.7, U1.37 (DOUT4)
DOUT5: J1.28, J4.9, U1.38 (DOUT5)
DOUT6: J1.30, J4.11, U1.40 (DOUT6)
DOUT7: J1.32, J4.13, U1.41 (DOUT7)
DOUT8: J1.34, U1.42 (DOUT8)
DOUT9: J1.36, U1.43 (DOUT9)
DOUT10: J1.38, U1.44 (DOUT10)
DOUT11: J1.40, U1.45 (DOUT11)
EXTCLK: J4.12, U1.31 (EXTCLK), Y1.3 (OUTPUT)
GND: C1.2, C2.2, C3.1, C4.1, C5.1, C6.1, C7.1, C8.2, C9.2, C10.2, C11.2, C12.2, IC1.2 (GND), IC2.2 (GND), IC2.7 (EP), J1.05, J1.06, J1.07, J1.10, J1.19, J1.21, J1.23, J1.25, J1.27, J1.33, J1.35, J2.2 (GND_1), J2.3 (GND_2), J4.2, J4.10, J4.23, J4.MP1, J4.MP2, R2.2, U1.2 (AGND), U1.3 (TEST), U1.6 (RSVD), U1.10 (DGND), U1.13 (SADDR), U1.17 (OE), U1.20 (TEST), U1.21 (TEST), U1.22 (AGND), U1.26 (DGND), U1.46 (DGND), U3.10 (GND), U3.12 (GND), U3.13 (GND), U3.24 (GND), Y1.2 (GND)
GPS_RF: J2.1 (SIGNAL), U3.11 (RF_IN)
GPS_RST: J1.17, R3.2, TP1.1, U3.8 (RSTN)
HSYNC: J1.14, J4.16, U1.8 (LINE_VALID)
unnamed: TP2.1, U3.1 (BOOT_SEL)
PXCLK: J1.08, J4.8, U1.32 (PIXCLK)
RESET: C7.2, J1.02, J4.19, R1.2, TP4.1, U1.16 (~RESET)
SCL: IC2.1 (SCL), J1.09, J4.20, U1.4 (SCLK)
SDA: IC2.4 (ADD0), IC2.6 (SDA), J1.11, J4.22, U1.5 (SDATA)
STANDBY: J1.13, R2.1, TP3.1, U1.14 (~STANDBY), Y1.1 (TRI-STATE)
STQ-PPS: U3.3 (1PPS)
STROBE: J1.16, J4.24, U1.9 (STROBE)
TRIGGER: J1.04, U1.15 (TRIGGER)
UART2_RX: J1.29, U3.21 (RXD)
UART2_TX: J1.31, U3.20 (TXD)
VSYNC: J1.12, J4.18, U1.7 (FRAME_VALID)

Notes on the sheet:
(This oscillator will clock both cameras)
2.8v Supply for Analog Core
OBC Connector
+-50 ppm
GPS Module
Temperature Sensor
48 Mhz Clock
Wide Angle Camera Ribbon Connector
200mA max 25 nA Iq
(OV5640 has internal 1.5v regulator)
Image Sensor

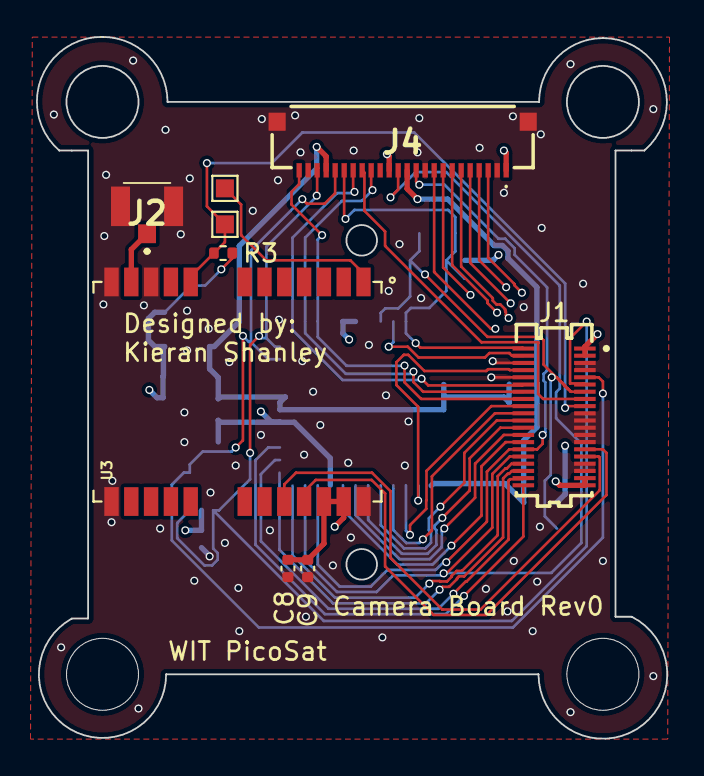
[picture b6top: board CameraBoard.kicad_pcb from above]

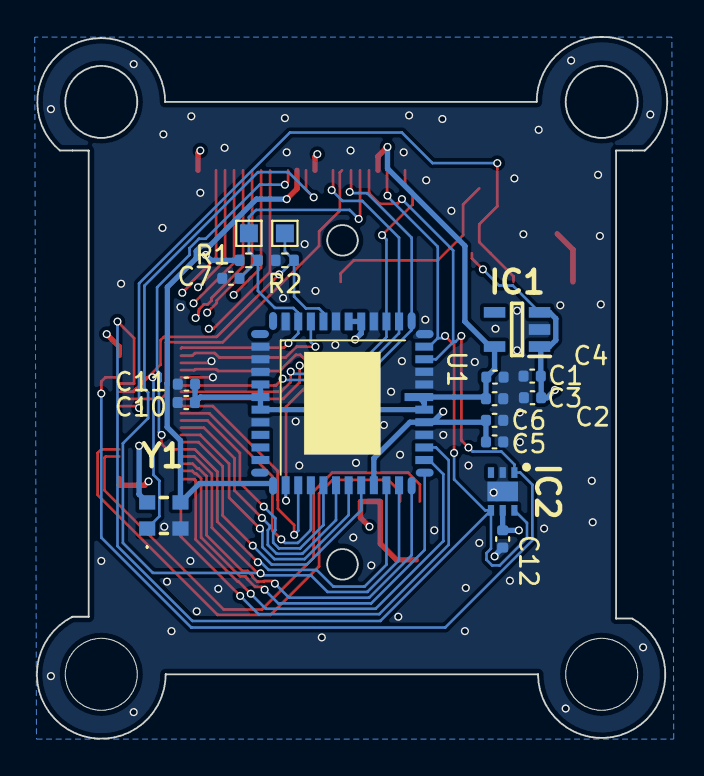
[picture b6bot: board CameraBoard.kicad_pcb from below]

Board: 4 copper layers, 35.0 x 39.0 mm, 27 parts (18 on the bottom side), 32 nets.
